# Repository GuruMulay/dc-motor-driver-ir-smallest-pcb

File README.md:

View this project on [CADLAB.io](https://cadlab.io/project/1364). 

Schematic and board files for a tiny, powerful DC motor driver.

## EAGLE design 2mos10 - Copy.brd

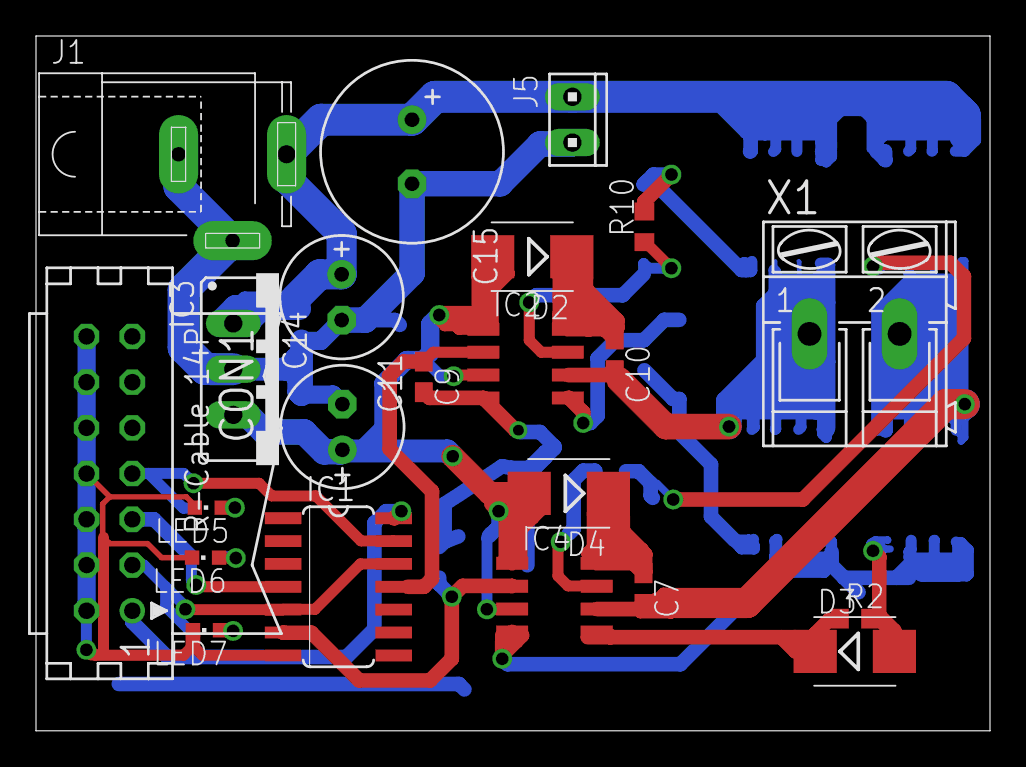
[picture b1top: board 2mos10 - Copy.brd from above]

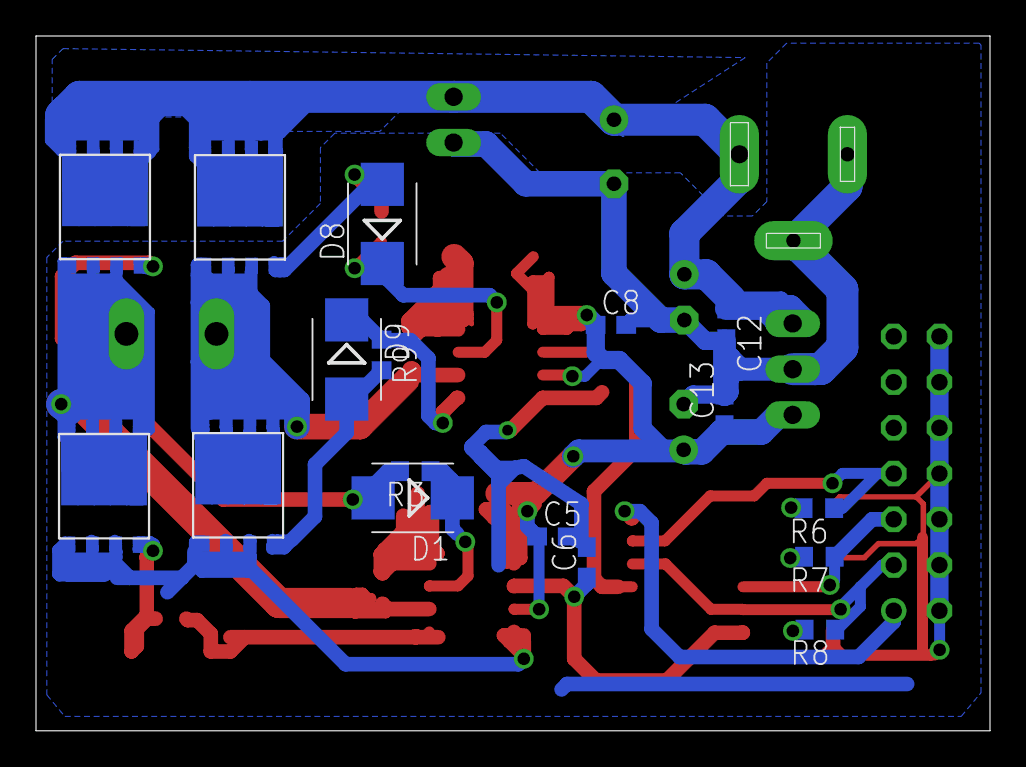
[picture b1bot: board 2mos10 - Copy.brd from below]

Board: 2 copper layers, 53.0 x 38.6 mm, 39 parts (17 on the bottom side), 24 nets.

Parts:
C5, C8: 10 uf; C0603
C6, C9: .01 uf; C0603
C7, C10: 1uf; C0603
C11: 100uf; E2,5-7
C12: .33uf; C0603
C13: .1uf; C0603
C14: 47uf; E2,5-7
C15: E3,5-10
CON1: CON14L
D1, D2, D3, D4, D8, D9: 1N5819; SMB
IC1: 74ACT00D; SO14
IC2, IC4: IR2520DS; SO08
IC3: 7818; 78XXS
J1: SPC4078
J5: 10X02MTA
LED5, LED6, LED7: CHIPLED_0603
R2, R3, R9, R10: 15ohm; R0603
R6, R7, R8: R0603
U$1, U$2, U$3, U$4: CSD18503GDS-NEW; CDS
X1: AK300/2

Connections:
5VCC: CON1.1, IC1.14
18V1: C5.1, C8.1, C13.1, C14.+, D2.A, D4.A, IC2.1, IC2.3, IC3.OUT, IC4.1, IC4.3
24V1: C11.+, C12.1, C15.+, IC3.IN, J1.3, J5.2, U$1.D1, U$1.D2, U$1.D3, U$1.D4, U$3.D1, U$3.D2, U$3.D3, U$3.D4
B1: CON1.7, IC1.13, R6.1
D1: CON1.5, IC1.4, R7.1
GND: C5.2, C6.2, C8.2, C9.2, C11.-, C12.2, C13.2, C14.-, C15.-, CON1.2, CON1.4, CON1.6, CON1.8, CON1.10, CON1.12, CON1.14, IC1.7, IC2.4, IC3.GND, IC4.4, J1.1, J1.2, J5.1, LED5.C, LED6.C, LED7.C, U$2.S1, U$2.S2, U$2.S3, U$4.S1, U$4.S2, U$4.S3
IN1: C9.1, IC1.11, IC2.2
IN2: C6.1, IC1.6, IC4.2
unnamed: D3.C, IC4.5, R2.1
unnamed: C7.2, IC4.6, U$3.S1, U$3.S2, U$3.S3, U$4.D1, U$4.D2, U$4.D3, U$4.D4, X1.2
unnamed: D8.A, R10.2, U$1.G
unnamed: D1.C, IC4.7, R3.1
unnamed: D1.A, R3.2, U$3.G
unnamed: D3.A, R2.2, U$4.G
unnamed: C10.2, IC2.6, U$1.S1, U$1.S2, U$1.S3, U$2.D1, U$2.D2, U$2.D3, U$2.D4, X1.1
unnamed: D9.C, IC2.5, R9.1
unnamed: D9.A, R9.2, U$2.G
unnamed: D8.C, IC2.7, R10.1
unnamed: LED5.A, R6.2
unnamed: LED6.A, R7.2
unnamed: LED7.A, R8.2
P1: CON1.3, IC1.5, IC1.12, R8.1
VB1: C10.1, D2.C, IC2.8
VB2: C7.1, D4.C, IC4.8

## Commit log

2015-10-25 Add entire project; Restructure all
2015-10-25 Add all
2018-10-11 Add schematics pdf
2018-10-11 Backlink to CADLAB.io has been added.
2018-10-13 fix name
2018-11-01 add on-load image
2018-11-01 add schematic image
2018-11-10 Add images
